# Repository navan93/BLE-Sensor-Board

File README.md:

# BLE Sensor Board
This is a flex PCB sensor board which can be used with the [Sensor Watch](https://github.com/joeycastillo/Sensor-Watch/tree/main) board by Joey Castillo. This is based on Nordic Semi's nRF52805 which is a tiny BLE SoC which is compatible with a 2 layer PCB. This adds BLE capabilities to the already awesome Sensor Watch.

[nRF52805](https://docs.nordicsemi.com/bundle/nRF52805_PS_v1.4/resource/nRF52805_PS_v1.4.pdf) has:
 - 64 MHz Arm Cortex-M4
 - 192 KB Flash + 24 KB RAM

It is configured in internal LDO regulator setup.

> [!CAUTION]
> The hardware is a bare minimum design which will make this work. For e.g the ANT pin is connected straight to a chip antenna, skipping all the filter/matching circuit, do not expect this to pass any certifications!!

## Pin Map
This pin map defines the electrical interface between the BLE Sensor Board (nRF52805)
and the Sensor Watch pins (A0–A4, SCL, SDA). The same mapping is also captured in
`FW/nrf52805-adv/hw/bsp/nrf52805/include/bsp/bsp.h` for use by the firmware BSP.

| **nRF Pin**      | **SAML22 Pin** | **Digital** | **Interrupt**   | **Analog**    | **I2C**             | **SPI**              | **UART**                 | **PWM**  | **Ext. Wake** |
| :---------:      | :------------: | :---------: | :-------------: | :-----------: | :-----------------: | :------------------: | :----------------------: | :------: | :-----------: |
| **P0.04**        | **D1**         | PB00        | EIC/EXTINT\[0\] | ADC/AIN\[8\]  | —                   | MISO<br>SERCOM3\[2\] | TX or RX<br>SERCOM3\[2\] | TC3\[0\] | RTC/IN\[0\]   |
| **P0.05**        | **D0**         | PB03        | EIC/EXTINT\[3\] | ADC/AIN\[11\] | —                   | CS<br>SERCOM3\[1\]   | RX<br>SERCOM3\[1\]       | TC2\[1\] | —             |
| **P0.12**        | **A2**         | PB02        | EIC/EXTINT\[2\] | ADC/AIN\[10\] | —                   | MOSI<br>SERCOM3\[0\] | TX or RX<br>SERCOM3\[0\] | TC2\[0\] | RTC/IN\[1\]   |
| **P0.16**        | **A1**         | PB01        | EIC/EXTINT\[1\] | ADC/AIN\[9\]  | —                   | SCK<br>SERCOM3\[3\]  | RX<br>SERCOM3\[3\]       | TC3\[1\] | —             |
| **P0.18**        | **SDA**        | —           | —               | —             | SDA<br>SERCOM1\[0\] | —                    | —                        | —        | —             |
| **NC**           | **SCL**        | —           | —               | —             | SCL<br>SERCOM1\[1\] | —                    | —                        | —        | —             |
| **P0.21/nReset** | **A0**         | PB04        | EIC/EXTINT\[4\] | ADC/AIN\[12\] | —                   | —                    | —                        | —        | —             |

## Features
1. Time sync - TBD
2. OTA update for Sensor Watch - TBD
3. OTA for Sensor board - TBD
4. Wireless Button - TBD

## Firmware
The firmware for this board is based on the [Apache Mynewt OS](https://mynewt.apache.org/).

### Setup
#### Toolchain
Install latest arm-gcc from the official [ARM release](https://developer.arm.com/downloads/-/arm-gnu-toolchain-downloads)

#### Debugger
Jlink, even a clone will do.

#### Mynewt OS

Install newt on MacOS
```
brew install go
git clone https://github.com/apache/mynewt-newt.git
cd mynewt-newt
make build
export PATH=$PWD/bin:$PATH
```

Install ARM toolchain
```
brew install gcc-arm-embedded
```

Initialize the project
```
cd FW/nrf52805_adv
newt upgrade --shallow=1
```
This step will take a bit of time as it pulls down the external repositories needed to build with Mynewt.

### Build
```
newt build nrf52_boot
newt build nrf52805_adv
newt create-image nrf52805_adv 1.0.0

newt build nrf52805_hid
newt create-image nrf52805_hid 0.1.0
```

### Upload
```
newt load nrf52_boot
newt load nrf52805_adv
newt load nrf52805_hid
```

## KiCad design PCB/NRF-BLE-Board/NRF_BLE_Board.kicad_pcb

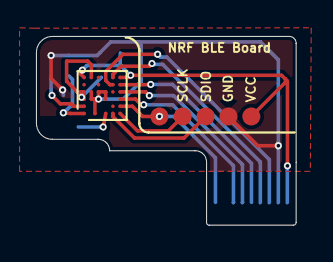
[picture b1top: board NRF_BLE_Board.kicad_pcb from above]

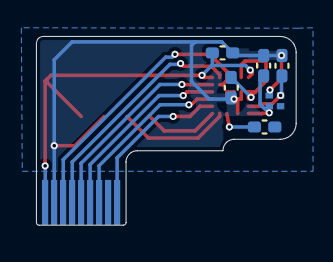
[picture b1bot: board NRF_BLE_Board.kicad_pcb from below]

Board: 2 copper layers, 14.4 x 10.5 mm, 10 parts (6 on the bottom side), 14 nets.

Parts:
AE1: Antenna; C_0402_1005Metric_Pad0.74x0.62mm_HandSolder
C1, C2: C; C_0402_1005Metric_Pad0.74x0.62mm_HandSolder
C4, C6: 1uF; C_0402_1005Metric_Pad0.74x0.62mm_HandSolder
J1: Conn_01x04; TestPoint_4Pads_Pitch1.27mm
TP3: TestPoint; TestPoint_Pad_D1.0mm
U1: nRF52805-CAxx; NRF_WLCSP-28_2.48x2.64mm_P0.4mm
U$1: FH19C-9S-0.5SH_10-FFC; FH19C9S05SH10-FFC
Y2: 32MHz; Crystal_SMD_Murata_XRCTD32M000N1P1AR0-4pin_1.2x1.0mm

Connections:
/GPIO0: U1.F6 (P0.05/AIN3), U$1.4
/GPIO1: U1.F5 (P0.04/AIN2), U$1.3
/GPIO2: U1.G5 (P0.12), U$1.5
/GPIO3: U1.G4 (P0.16), U$1.6
/GPIO4: U1.G3 (P0.18), U$1.7
/SWDCLK: J1.4, U1.G1 (SWDCLK)
/SWDIO: J1.3, U1.F1 (SWDIO)
/nReset: TP3.1, U1.G2 (P0.21/nRESET), U$1.9
GND: C1.1, C2.1, C4.2, C6.2, J1.2, U1.B3 (VSS), U1.B4 (VSS), U1.C1 (VSS_PA), U1.D3 (VSS), U1.D4 (VSS), U1.E3 (VSS), U1.E4 (VSS), U$1.2, Y2.2
unnamed: AE1.1 (A), U1.E1 (ANT)
unnamed: C6.1, U1.A3 (DEC2), U1.A4 (DEC4), U1.B6 (DEC1)
unnamed: C1.2, U1.A1 (XC1), Y2.3
unnamed: C2.2, U1.A2 (XC2), Y2.1
VCC: C4.1, J1.1, U1.A6 (VDD), U1.G6 (VDD), U$1.1

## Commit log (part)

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2025-03-17 Add PCB files
2025-03-17 Add some intro
2025-03-17 Init mynewt app
2025-03-17 Setup basic advertising app, build pass
2025-04-04 We have advertisements!!
2025-04-04 Fix download and debug using openocd and jlink
2025-04-05 Add a basic BLE scanner web app
2025-04-05 Restructure to be compatible with gh pages
2025-04-05 Some cleanup
2025-04-05 Reduce code size
2026-03-20 Add BLE HID keyboard demo for nRF52805 sensor board
2026-03-20 Refactor HID keyboard to use generic hid_send_keycode() function
2026-03-23 Add modifier key support to HID keyboard using hid_keyboard_input struct
2026-03-26 Add BLE HID keyboard functionality and enhance project configuration
    - Introduced HID keyboard support with necessary input/output reports.
    - Updated GATT service definitions for HID and Device Information services.
    - Enhanced console input handling for sending HID keycodes.
    - Modified project configuration files for improved logging and console input.
    - Added instructions for installing the ARM toolchain and initializing the project.
2026-03-27 Refactor HID keyboard report structure and update descriptors for improved functionality. Keys now work with iOS.
2026-03-27 Add UART support and update configuration for BLE HID demo
2026-03-29 Fix mistakes in pinmap
2026-03-29 Add initial implementation of Hello World application with configuration files
2026-03-29 Refactor Hello World application to integrate UART driver
    - Updated README.md to reflect the new UART driver framework for Apache Mynewt.
    - Modified pkg.yml to change console dependency from full to minimal and added UART dependency.
    - Enhanced main.c to implement UART initialization, RX/TX callbacks, and event handling for received data.
    - Adjusted syscfg.yml to enable UART configuration.
    - Updated board-specific syscfg.yml to correct UART pin mappings.
    - Revised README.md to clarify pin mappings between nRF and SAML22.
2026-03-31 Update syscfg.yml to adjust console implementation settings for minimal logging
